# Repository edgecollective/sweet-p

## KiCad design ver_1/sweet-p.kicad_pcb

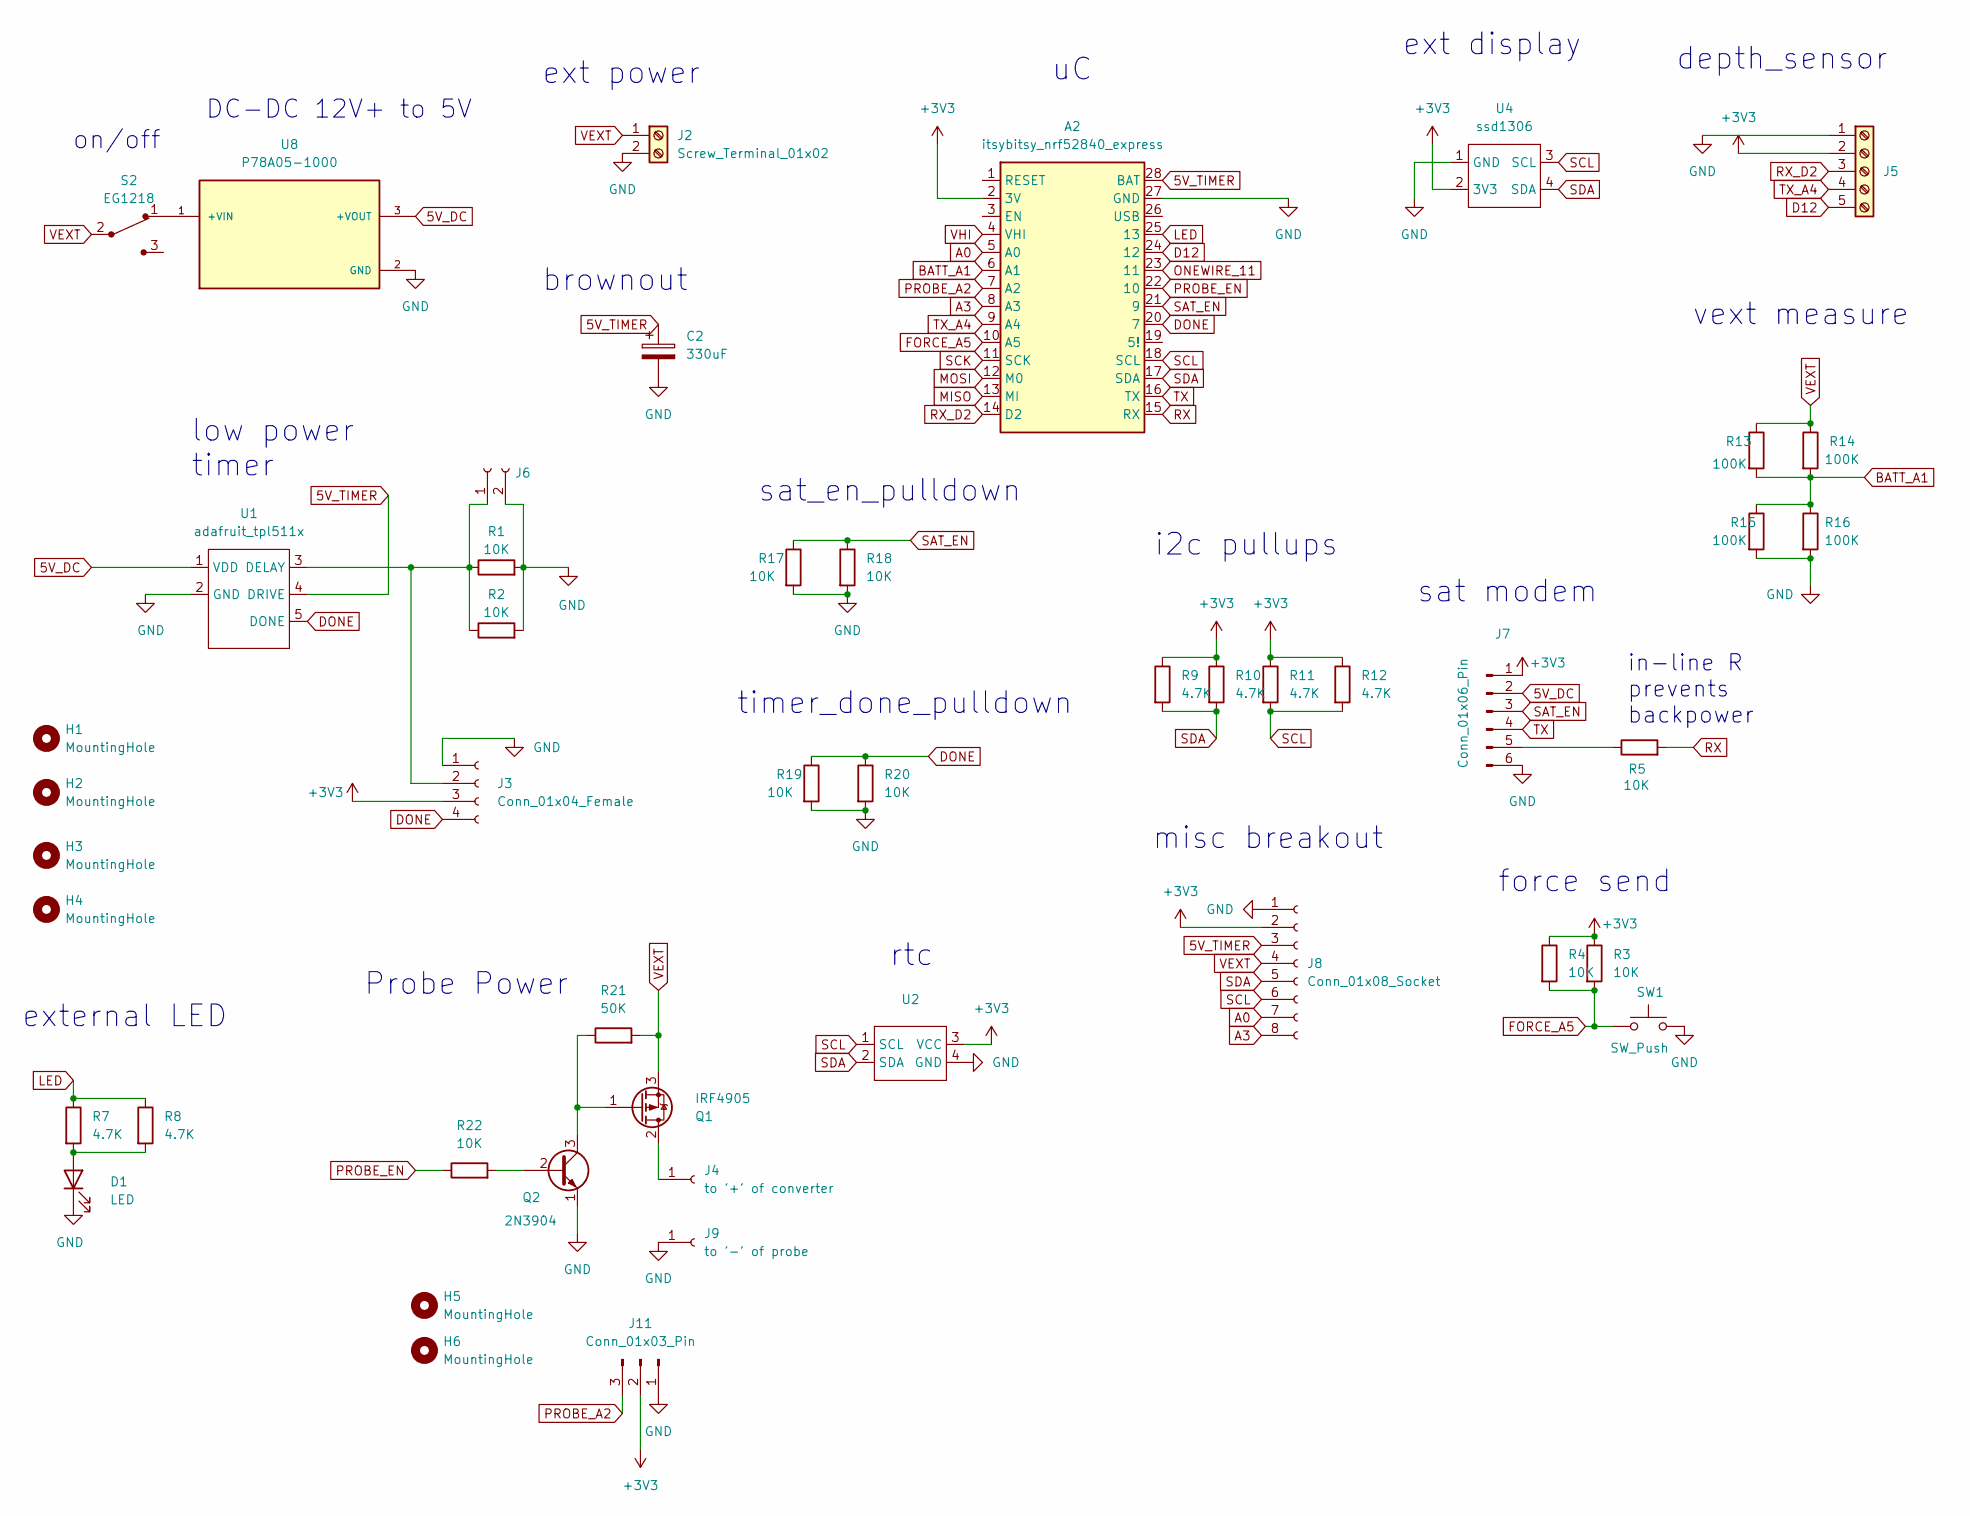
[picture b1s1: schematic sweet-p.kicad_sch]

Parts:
A2: itsybitsy_nrf52840_express; itsybitsy
C2: 330uF; CP_Radial_D5.0mm_P2.00mm
D1: LED; LED_D5.0mm
H1, H2, H3, H4, H5, H6: MountingHole; MountingHole_3.2mm_M3
J2: Screw_Terminal_01x02; TerminalBlock_Phoenix_PT-1,5-2-5.0-H_1x02_P5.00mm_Horizontal
J3: Conn_01x04_Female; PinSocket_1x04_P2.54mm_Vertical
J4: to '+' of converter; PinSocket_1x01_P2.54mm_Vertical
J5: Screw_Terminal_01x05; TerminalBlock_Phoenix_MKDS-1,5-5-5.08_1x05_P5.08mm_Horizont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
J6: Conn_01x02_Socket; PinSocket_1x02_P2.54mm_Vertical
J7: Conn_01x06_Pin; PinHeader_1x06_P2.54mm_Vertical
J8: Conn_01x08_Socket; PinSocket_1x08_P2.54mm_Vertical
J9: to '-' of probe; PinSocket_1x01_P2.54mm_Vertical
J11: Conn_01x03_Pin; PinHeader_1x03_P2.54mm_Vertical
Q1: IRF4905; TO-220-3_Vertical
Q2: 2N3904; TO-92_Inline
R1, R3, R18, R20: 10K; R_0603_1608Metric_Pad0.98x0.95mm_HandSolder
R2, R4, R5, R17, R19, R22: 10K; R_Axial_DIN0204_L3.6mm_D1.6mm_P7.62mm_Horizontal
R7, R9, R12: 4.7K; R_Axial_DIN0204_L3.6mm_D1.6mm_P7.62mm_Horizontal
R8, R10, R11: 4.7K; R_0603_1608Metric_Pad0.98x0.95mm_HandSolder
R13, R15: 100K; R_Axial_DIN0204_L3.6mm_D1.6mm_P7.62mm_Horizontal
R14, R16: 100K; R_0603_1608Metric_Pad0.98x0.95mm_HandSolder
R21: 50K; R_Axial_DIN0204_L3.6mm_D1.6mm_P7.62mm_Horizontal
S2: EG1218; Switch_Slide_11.6x4mm_EG1218; MPN EG1218; Digi-Key_PN EG1903-ND
SW1: SW_Push; SW_PUSH_6mm
U1: adafruit_tpl511x
U2: ds3231_amazon
U4: ssd1306; ssd1306_a
U8: P78A05-1000; CONV_P78A05-1000; PARTREV 1.0

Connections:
5V_DC: J7.2, U1.1 (VDD), U8.3 (+VOUT)
5V_TIMER: A2.28 (BAT), C2.1, J8.3, U1.4 (DRIVE)
+3V3: A2.2 (3V), J3.3, J5.2, J7.1, J8.2, J11.2, R3.1, R4.1, R9.1, R10.1, R11.1, R12.1, U2.3 (VCC), U4.2 (3V3)
A0: A2.5 (A0), J8.7
A3: A2.8 (A3), J8.8
BATT_A1: A2.6 (A1), R13.2, R14.2, R15.1, R16.1
D12: A2.24 (12), J5.5
DONE: A2.20 (7), J3.4, R19.1, R20.1, U1.5 (DONE)
FORCE_A5: A2.10 (A5), R3.2, R4.2, SW1.1
GND: A2.27 (GND), C2.2, D1.1 (K), J2.2, J3.1, J5.1, J6.2, J7.6, J8.1, J9.1, J11.1, Q2.1 (E), R1.2, R2.2, R15.2, R16.2, R17.2, R18.2, R19.2, R20.2, SW1.2, U1.2 (GND), U2.4 (GND), U4.1 (GND), U8.2 (GND)
LED: A2.25 (13), R7.1, R8.1
MISO: A2.13 (MI)
MOSI: A2.12 (M0)
unnamed: D1.2 (A), R7.2, R8.2
unnamed: J3.2, J6.1, R1.1, R2.1, U1.3 (DELAY)
unnamed: J4.1, Q1.2 (D)
unnamed: J7.5, R5.1
unnamed: Q1.1 (G), Q2.3 (C), R21.1
unnamed: Q2.2 (B), R22.2
unnamed: S2.1, U8.1 (+VIN)
ONEWIRE_11: A2.23 (11)
PROBE_A2: A2.7 (A2), J11.3
PROBE_EN: A2.22 (10), R22.1
RX: A2.15 (RX), R5.2
RX_D2: A2.14 (D2), J5.3
SAT_EN: A2.21 (9), J7.3, R17.1, R18.1
SCK: A2.11 (SCK)
SCL: A2.18 (SCL), J8.6, R11.2, R12.2, U2.1 (SCL), U4.3 (SCL)
SDA: A2.17 (SDA), J8.5, R9.2, R10.2, U2.2 (SDA), U4.4 (SDA)
TX: A2.16 (TX), J7.4
TX_A4: A2.9 (A4), J5.4
VEXT: J2.1, J8.4, Q1.3 (S), R13.1, R14.1, R21.2, S2.2
VHI: A2.4 (VHI)

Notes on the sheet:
force send
sat modem
brownout
DC-DC 12V+ to 5V
sat_en_pulldown
vext measure
misc breakout
timer_done_pulldown
in-line R prevents backpower
on/off
i2c pullups
external LED
depth_sensor
low power timer
ext power
ext display
Probe Power
rtc

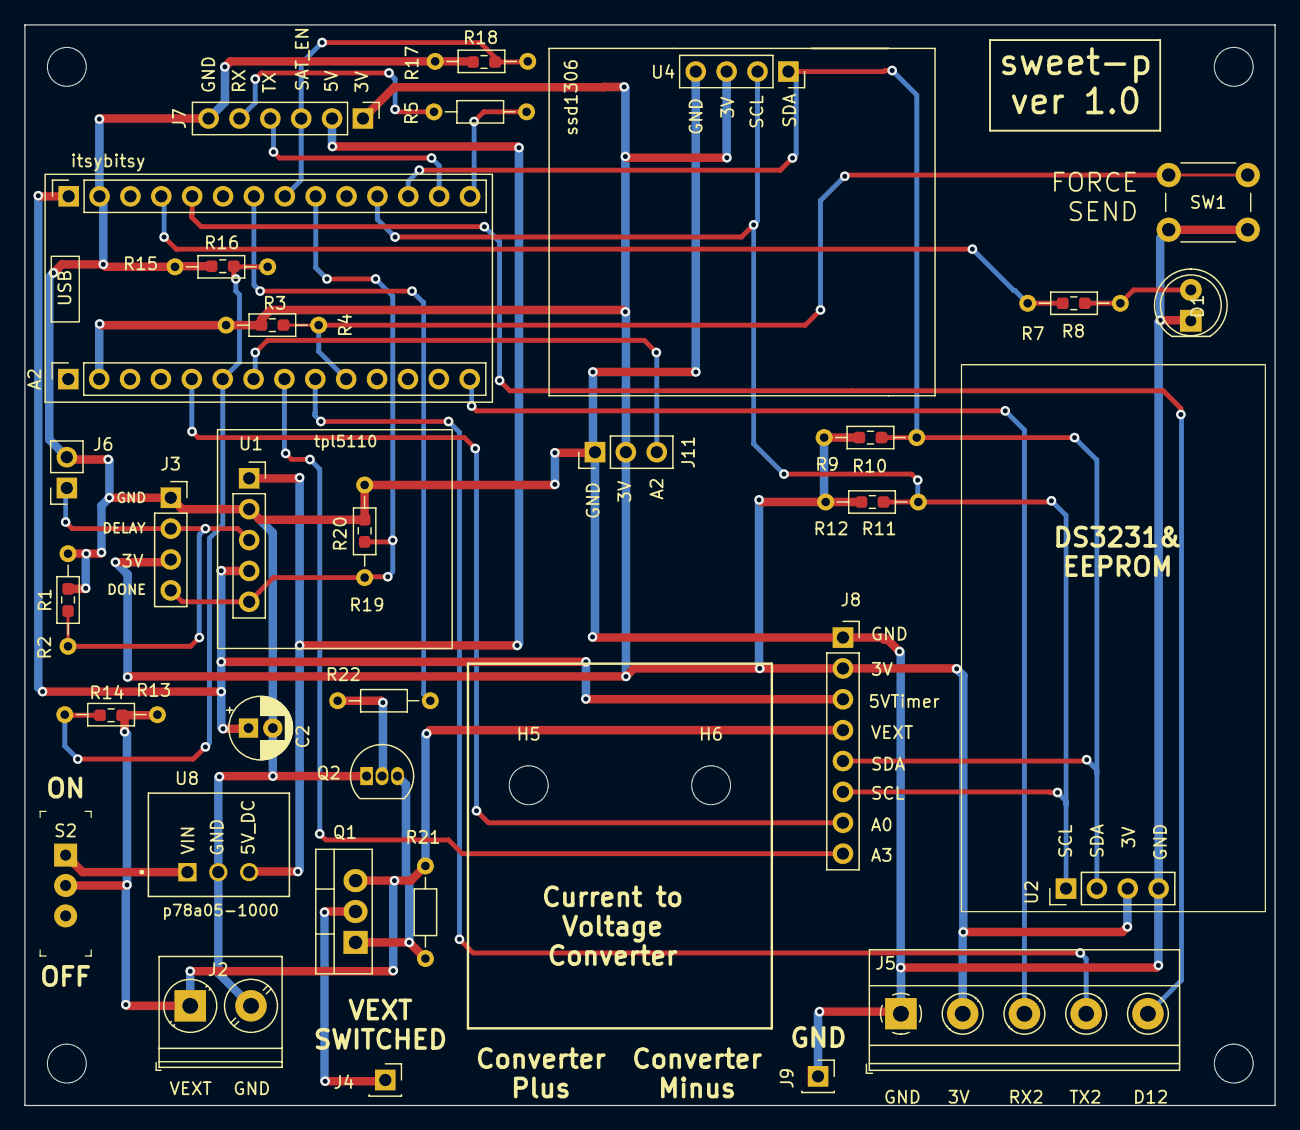
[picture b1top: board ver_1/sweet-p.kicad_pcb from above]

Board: 2 copper layers, 102.8 x 88.9 mm, 47 parts (0 on the bottom side), 28 nets.

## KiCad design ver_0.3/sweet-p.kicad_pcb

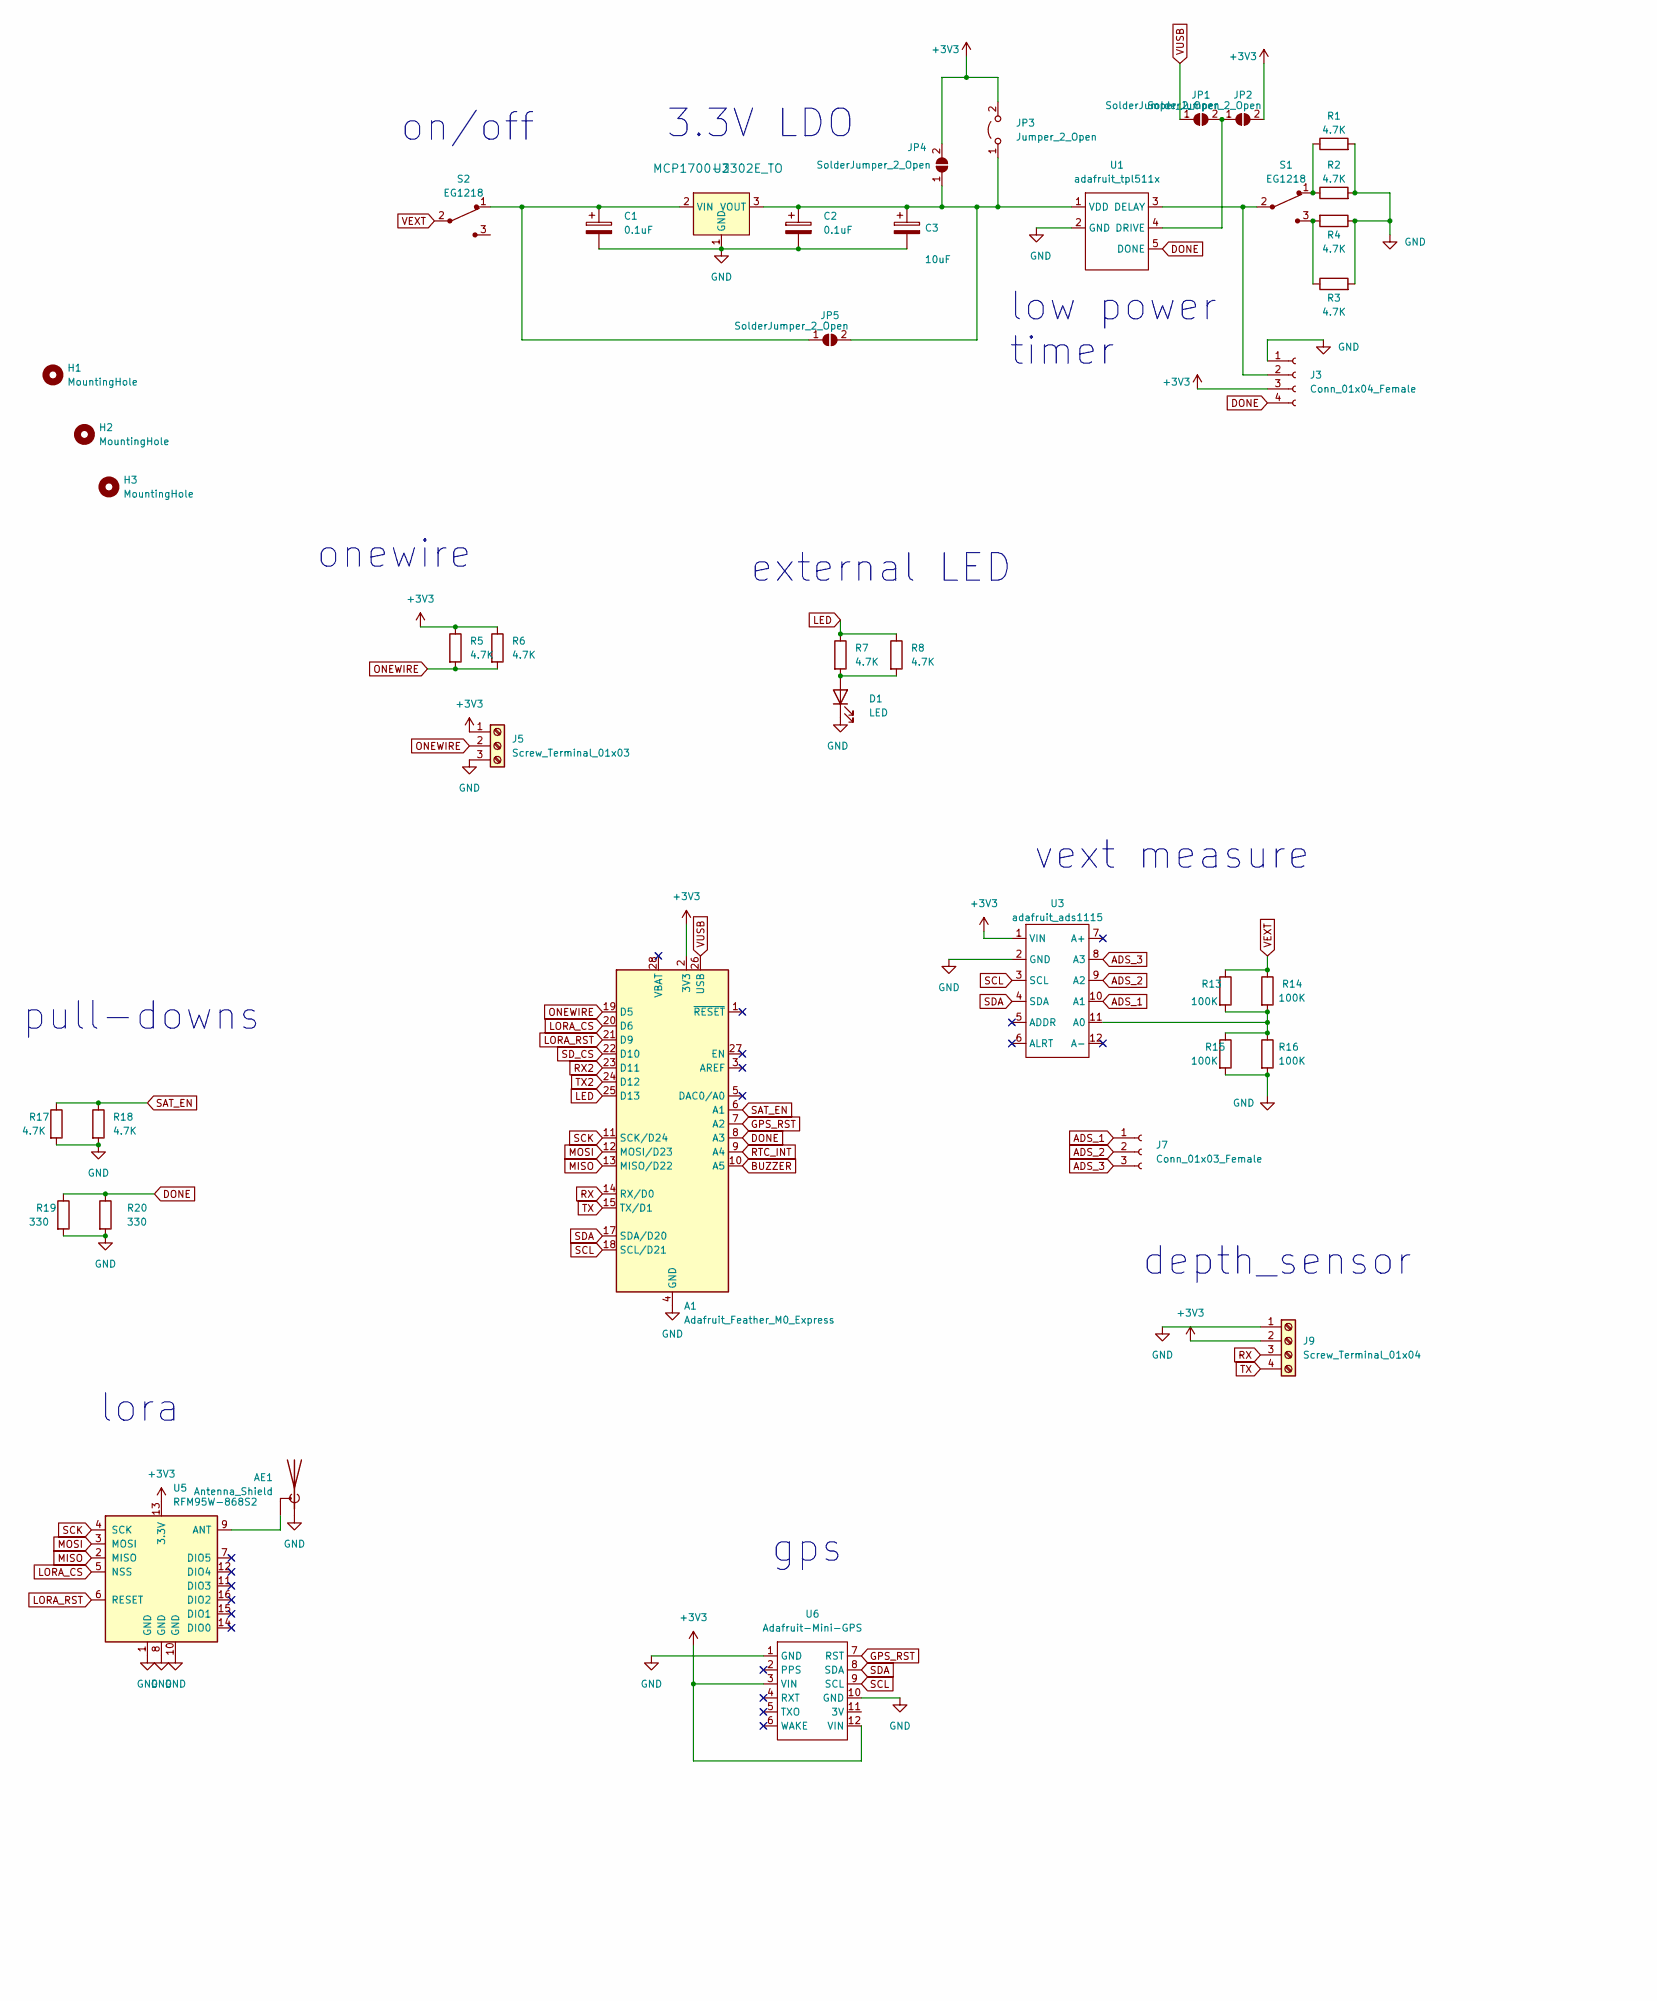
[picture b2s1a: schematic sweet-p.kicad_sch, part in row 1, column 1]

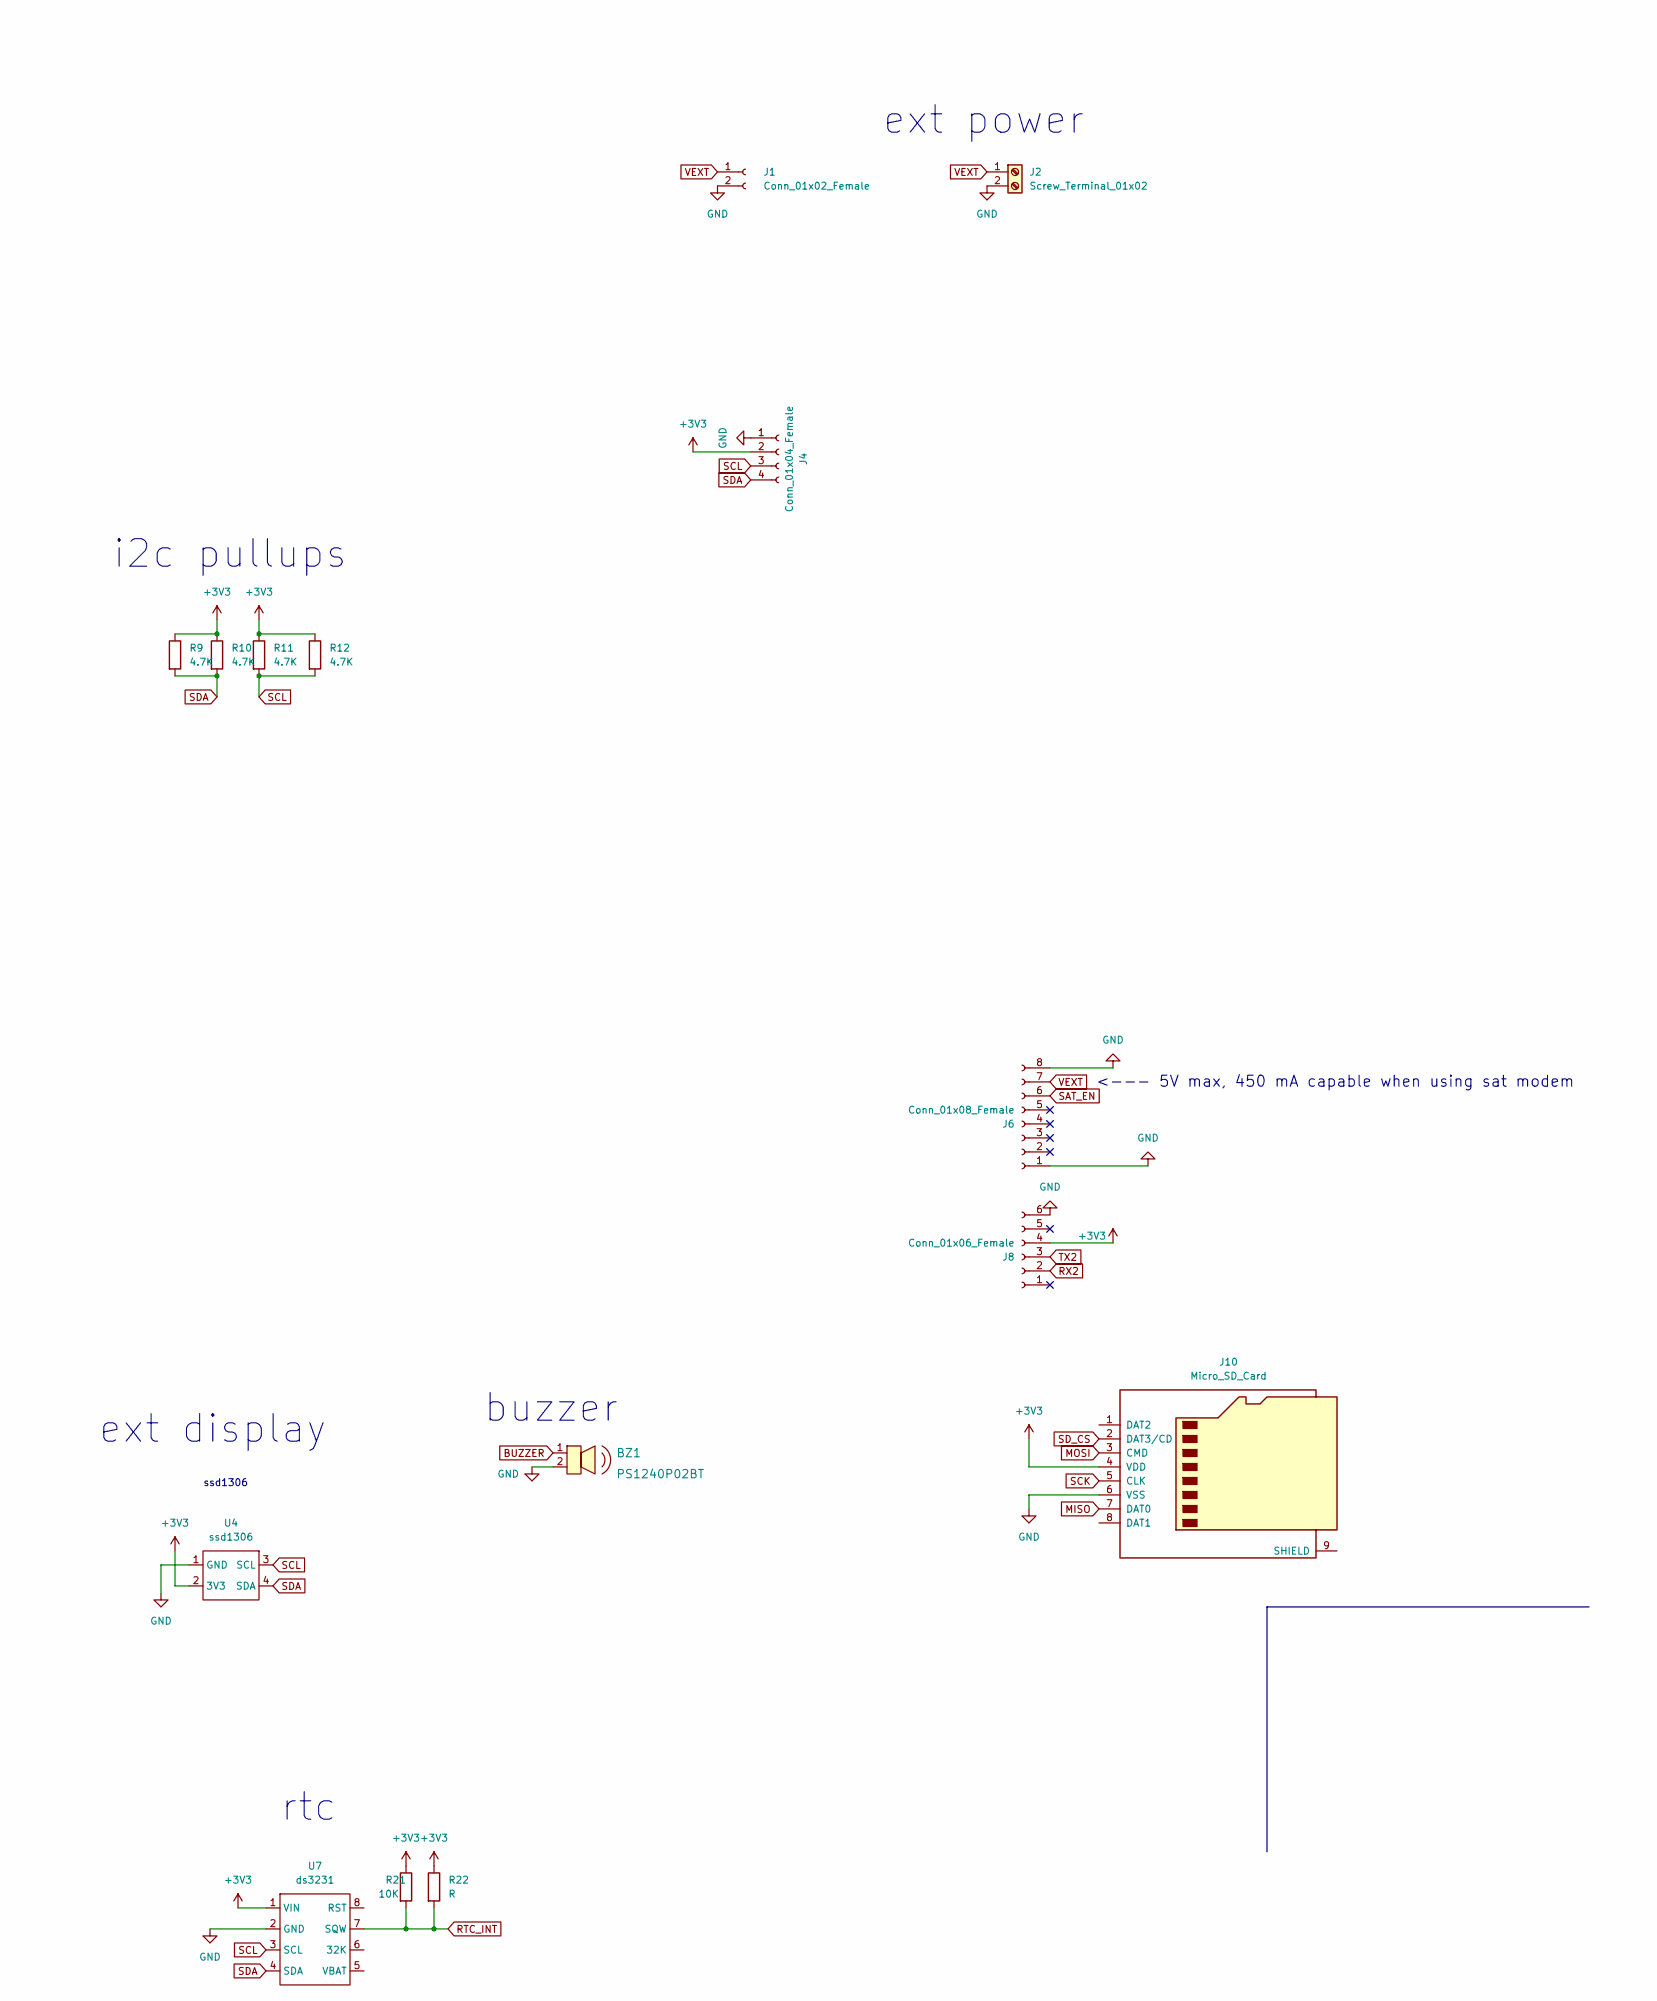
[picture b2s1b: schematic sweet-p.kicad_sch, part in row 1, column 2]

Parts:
A1: Adafruit_Feather_M0_Express; Adafruit_Feather
AE1: Antenna_Shield; RF_SMA_Vertical_5-1814832-1
BZ1: PS1240P02BT; Piezo_Transducer_THT_PS1240P02BT; MPN PS1240P02BT; Digi-Key_PN 445-2525-1-ND
C1, C2: 0.1uF; CP_Radial_Tantal_D4.5mm_P2.50mm
C3: 10uF; CP_Radial_Tantal_D4.5mm_P2.50mm
D1: LED; LED_D5.0mm
H1, H2, H3: MountingHole; MountingHole_3.2mm_M3
J1: Conn_01x02_Female; JST_PH_B2B-PH-K_1x02_P2.00mm_Vertical
J2: Screw_Terminal_01x02; TerminalBlock_Phoenix_PT-1,5-2-5.0-H_1x02_P5.00mm_Horizontal
J3, J4: Conn_01x04_Female; PinSocket_1x04_P2.54mm_Vertical
J5: Screw_Terminal_01x03; TerminalBlock_Phoenix_PT-1,5-3-5.0-H_1x03_P5.00mm_Horizontal
J6: Conn_01x08_Female; PinSocket_1x08_P2.54mm_Vertical
J7: Conn_01x03_Female; PinSocket_1x03_P2.54mm_Vertical
J8: Conn_01x06_Female; PinSocket_1x06_P2.54mm_Vertical
J9: Screw_Terminal_01x04; TerminalBlock_Phoenix_PT-1,5-4-5.0-H_1x04_P5.00mm_Horizontal
J10: Micro_SD_Card; DM3D-SF_outline
JP1, JP2, JP4, JP5: SolderJumper_2_Open; SolderJumper-2_P1.3mm_Open_Pad1.0x1.5mm
JP3: Jumper_2_Open; PinHeader_1x02_P2.54mm_Vertical
R1, R3, R6, R8, R10, R11, R18: 4.7K; R_0603_1608Metric_Pad0.98x0.95mm_HandSolder
R2, R4, R5, R7, R9, R12, R17: 4.7K; R_Axial_DIN0204_L3.6mm_D1.6mm_P7.62mm_Horizontal
R13, R15: 100K; R_Axial_DIN0204_L3.6mm_D1.6mm_P7.62mm_Horizontal
R14, R16: 100K; R_0603_1608Metric_Pad0.98x0.95mm_HandSolder
R19: 330; R_Axial_DIN0204_L3.6mm_D1.6mm_P7.62mm_Horizontal
R20: 330; R_0603_1608Metric_Pad0.98x0.95mm_HandSolder
R21: 10K; R_0603_1608Metric_Pad0.98x0.95mm_HandSolder
R22: R; R_Axial_DIN0204_L3.6mm_D1.6mm_P7.62mm_Horizontal
S1, S2: EG1218; Switch_Slide_11.6x4mm_EG1218; MPN EG1218; Digi-Key_PN EG1903-ND
U1: adafruit_tpl511x
U2: MCP1700-3302E_TO; TO-92-3; MPN MCP1700-3302E/TO; Digi-Key_PN MCP1700-3302E/TO-ND
U3: adafruit_ads1115
U4: ssd1306; ssd1306_a
U5: RFM95W-868S2; HOPERF_RFM9XW_SMD
U6: Adafruit-Mini-GPS; adafruit_mini_gps
U7: ds3231; ds3231_adafruit_breakout

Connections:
+3V3: A1.2 (3V3), J3.3, J4.2, J5.1, J8.4, J9.2, J10.4 (VDD), JP2.2 (B), JP3.2 (B), JP4.2 (B), R5.1, R6.1, R9.1, R10.1, R11.1, R12.1, R21.1, R22.1, U3.1 (VIN), U4.2 (3V3), U5.13 (3.3V), U6.3 (VIN), U6.12 (VIN), U7.1 (VIN)
ADS_1: J7.1, U3.10 (A1)
ADS_2: J7.2, U3.9 (A2)
ADS_3: J7.3, U3.8 (A3)
BUZZER: A1.10 (A5), BZ1.1
DONE: A1.8 (A3), J3.4, R19.1, R20.1, U1.5 (DONE)
GND: A1.4 (GND), A1.16 (GND), AE1.1 (A), BZ1.2, C1.2, C2.2, C3.2, D1.1 (K), J1.2, J2.2, J3.1, J4.1, J5.3, J6.1, J6.8, J8.6, J9.1, J10.6 (VSS), R1.2, R2.2, R3.1, R4.2, R15.2, R16.2, R17.2, R18.2, R19.2, R20.2, U1.2 (GND), U2.1 (GND), U3.2 (GND), U4.1 (GND), U5.1 (GND), U5.8 (GND), U5.10 (GND), U6.1 (GND), U6.10 (GND), U7.2 (GND)
GPS_RST: A1.7 (A2), U6.7 (RST)
LED: A1.25 (D13), R7.1, R8.1
LORA_CS: A1.20 (D6), U5.5 (NSS)
LORA_RST: A1.21 (D9), U5.6 (RESET)
MISO: A1.13 (MISO/D22), J10.7 (DAT0), U5.2 (MISO)
MOSI: A1.12 (MOSI/D23), J10.3 (CMD), U5.3 (MOSI)
unnamed: AE1.2 (Shield), U5.9 (ANT)
unnamed: C1.1, JP5.1 (A), S2.1, U2.2 (VIN)
unnamed: C2.1, C3.1, JP3.1 (A), JP4.1 (A), JP5.2 (B), U1.1 (VDD), U2.3 (VOUT)
unnamed: D1.2 (A), R7.2, R8.2
unnamed: R1.1, R2.1, S1.1
unnamed: R3.2, R4.1, S1.3
unnamed: R13.2, R14.2, R15.1, R16.1, U3.11 (A0)
unnamed: J3.2, S1.2, U1.3 (DELAY)
unnamed: JP1.2 (B), JP2.1 (A), U1.4 (DRIVE)
ONEWIRE: A1.19 (D5), J5.2, R5.2, R6.2
RTC_INT: A1.9 (A4), R21.2, R22.2, U7.7 (SQW)
RX: A1.14 (RX/D0), J9.3
RX2: A1.23 (D11), J8.2
SAT_EN: A1.6 (A1), J6.6, R17.1, R18.1
SCK: A1.11 (SCK/D24), J10.5 (CLK), U5.4 (SCK)
SCL: A1.18 (SCL/D21), J4.3, R11.2, R12.2, U3.3 (SCL), U4.3 (SCL), U6.9 (SCL), U7.3 (SCL)
SDA: A1.17 (SDA/D20), J4.4, R9.2, R10.2, U3.4 (SDA), U4.4 (SDA), U6.8 (SDA), U7.4 (SDA)
SD_CS: A1.22 (D10), J10.2 (DAT3/CD)
TX: A1.15 (TX/D1), J9.4
TX2: A1.24 (D12), J8.3
VEXT: J1.1, J2.1, J6.7, R13.1, R14.1, S2.2
VUSB: A1.26 (USB), JP1.1 (A)

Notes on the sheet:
buzzer
pull-downs
vext measure
gps
lora
<--- 5V max, 450 mA capable when using sat modem
onewire
on/off
i2c pullups
external LED
depth_sensor
low power timer
ext power
ext display
ssd1306
3.3V LDO
rtc

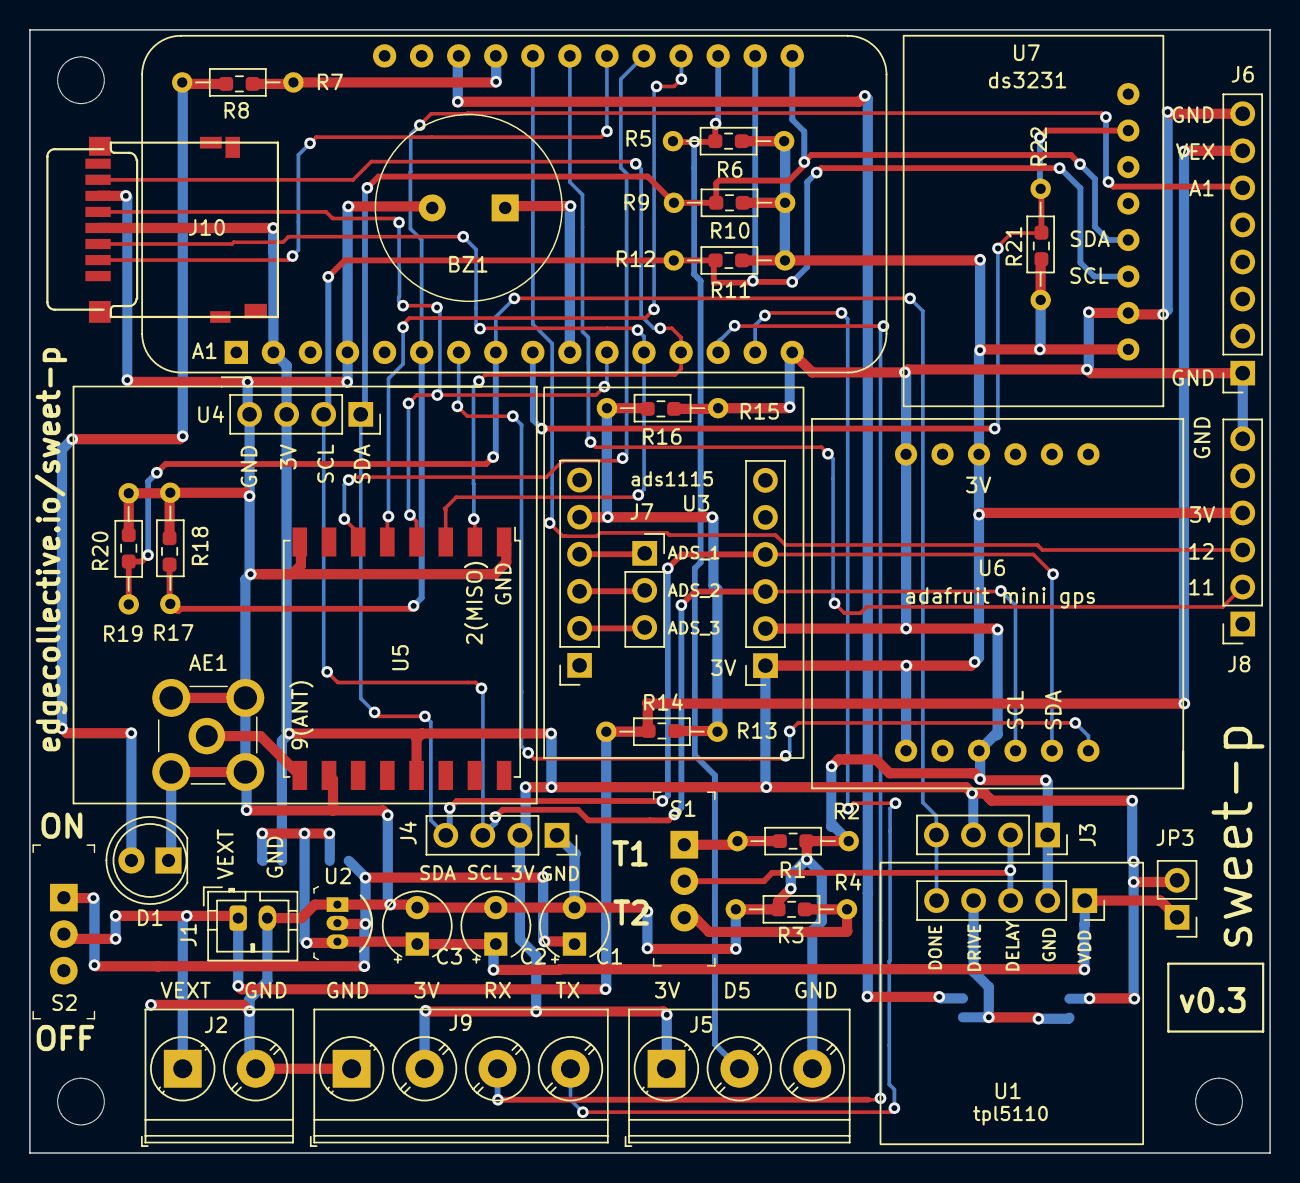
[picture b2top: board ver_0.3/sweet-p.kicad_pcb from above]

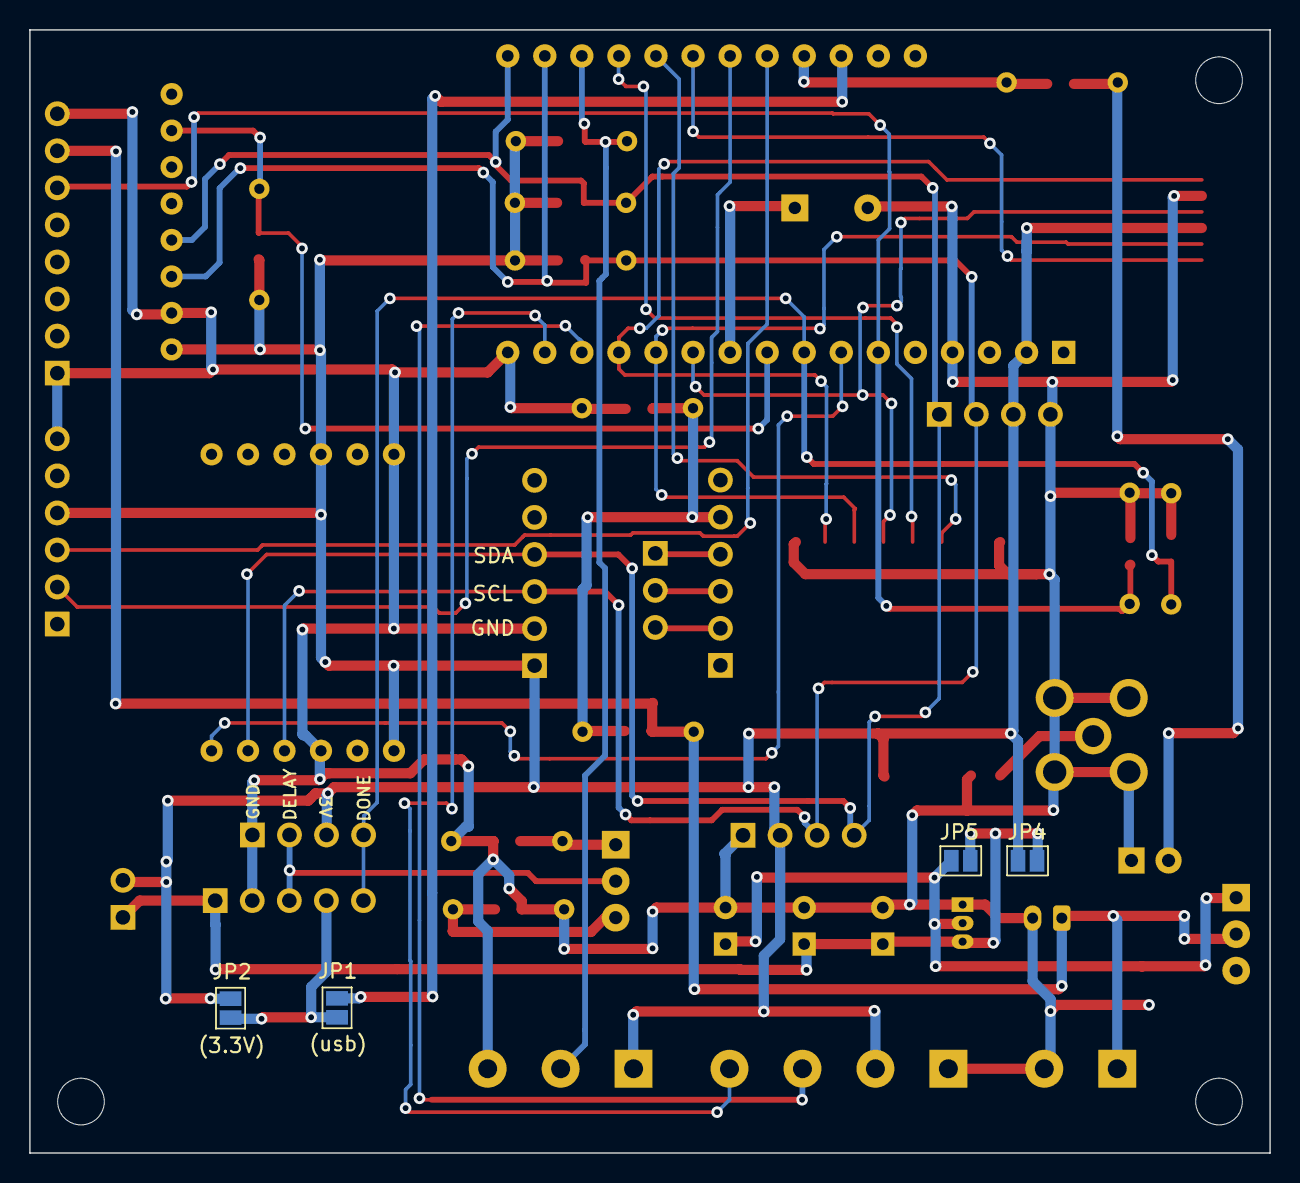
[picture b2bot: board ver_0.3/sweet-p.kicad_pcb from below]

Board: 2 copper layers, 85.0 x 77.0 mm, 56 parts (4 on the bottom side), 35 nets.
